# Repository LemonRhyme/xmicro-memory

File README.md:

# XMICRO-MEMORY

[XMICRO](https://github.com/x-microsystems/xmicro-bus) card providing 1MB of RAM and an optional relocatable 8KB EEPROM.

[Datasheet](Documentation/XMICRO-MEMORY.pdf)

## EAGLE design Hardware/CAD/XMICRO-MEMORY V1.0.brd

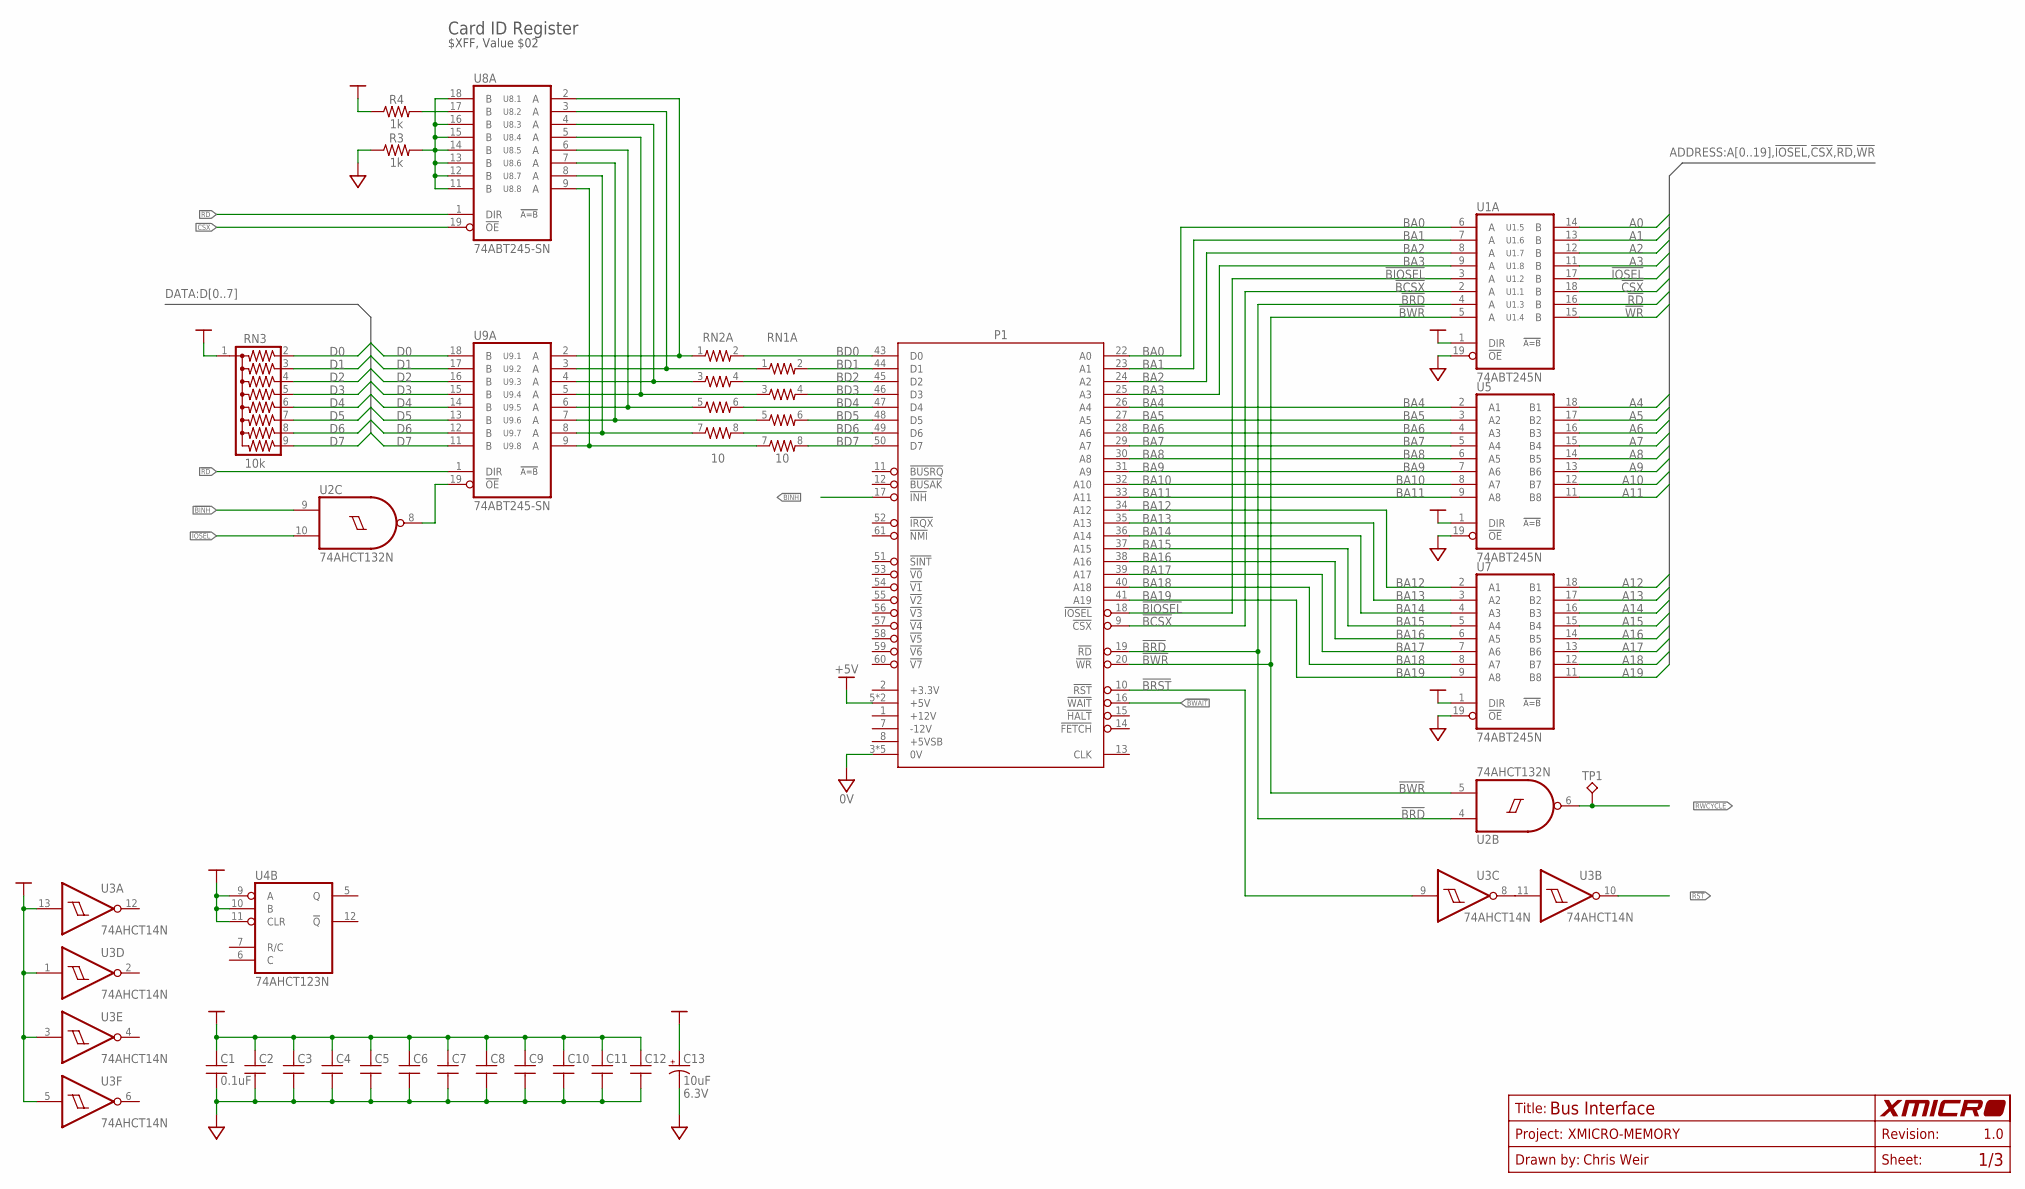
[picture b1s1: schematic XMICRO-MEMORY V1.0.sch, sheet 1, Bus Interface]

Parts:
C1, C2, C3, C4, C5, C6, C7, C8, C9, C10, C11, C12: 0.1uF; C025-024X044
C13: 10uF; E2,5-6; VOLTAGE 6.3V
P1: XMICRO-BUS-EDGE; EDGE62M
R3, R4: 1k; 0207/10
RN1, RN2: 10; SIL8
RN3: 10k; SIL9
TP1: TP-040
U1, U5, U7: 74ABT245N; DIL20
U2: 74AHCT132N; DIL14
U3: 74AHCT14N; DIL14
U4: 74AHCT123N; DIL16
U8, U9: 74ABT245-SN; DIL20

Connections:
0V: C1.2, C2.2, C3.2, C4.2, C5.2, C6.2, C7.2, C8.2, C9.2, C10.2, C11.2, C12.2, C13.-, P1.3 (0V), P1.4 (0V), P1.21 (0V), P1.42 (0V), P1.62 (0V), R3.1, U1.10 (0V), U1.19 (!OE), U2.7 (0V), U3.7 (0V), U4.8 (0V), U5.10 (0V), U5.19 (!OE), U7.10 (0V), U7.19 (!OE), U8.10 (0V), U9.10 (0V); also elsewhere on the board
!BCSX: P1.9 (!CSX), U1.2 (A)
!BINH: P1.17 (!INH), U2.9 (I0); also elsewhere on the board
!BIOSEL: P1.18 (!IOSEL), U1.3 (A)
!BRD: P1.19 (!RD), U1.4 (A), U2.4 (I0)
!BRST: P1.10 (!RST), U3.9 (I)
!BWAIT: P1.16 (!WAIT); also elsewhere on the board
!BWR: P1.20 (!WR), U1.5 (A), U2.5 (I1)
!CSX: U1.18 (B), U8.19 (!OE)
!IOSEL: U1.17 (B), U2.10 (I1); also elsewhere on the board
!RD: U1.16 (B), U8.1 (DIR), U9.1 (DIR); also elsewhere on the board
!RST: U3.10 (O); also elsewhere on the board
!WR: U1.15 (B); also elsewhere on the board
+5V: C1.1, C2.1, C3.1, C4.1, C5.1, C6.1, C7.1, C8.1, C9.1, C10.1, C11.1, C12.1, C13.+, P1.5 (+5V), P1.6 (+5V), R4.1, RN3.1, U1.1 (DIR), U1.20 (+5V), U2.14 (+5V), U3.1 (I), U3.3 (I), U3.5 (I), U3.13 (I), U3.14 (+5V), U4.9 (A), U4.10 (B), U4.11 (CLR), U4.16 (+5V), U5.1 (DIR), U5.20 (+5V), U7.1 (DIR), U7.20 (+5V), U8.20 (+5V), U9.20 (+5V); also elsewhere on the board
A0: U1.14 (B); also elsewhere on the board
A1: U1.13 (B); also elsewhere on the board
A2: U1.12 (B); also elsewhere on the board
A3: U1.11 (B); also elsewhere on the board
A4: U5.18 (B1); also elsewhere on the board
A5: U5.17 (B2); also elsewhere on the board
A6: U5.16 (B3); also elsewhere on the board
A7: U5.15 (B4); also elsewhere on the board
A8: U5.14 (B5); also elsewhere on the board
A9: U5.13 (B6); also elsewhere on the board
A10: U5.12 (B7); also elsewhere on the board
A11: U5.11 (B8); also elsewhere on the board
A12: U7.18 (B1); also elsewhere on the board
A13: U7.17 (B2); also elsewhere on the board
A14: U7.16 (B3); also elsewhere on the board
A15: U7.15 (B4); also elsewhere on the board
A16: U7.14 (B5); also elsewhere on the board
A17: U7.13 (B6); also elsewhere on the board
A18: U7.12 (B7); also elsewhere on the board
A19: U7.11 (B8); also elsewhere on the board
BA0: P1.22 (A0), U1.6 (A)
BA1: P1.23 (A1), U1.7 (A)
BA2: P1.24 (A2), U1.8 (A)
BA3: P1.25 (A3), U1.9 (A)
BA4: P1.26 (A4), U5.2 (A1)
BA5: P1.27 (A5), U5.3 (A2)
BA6: P1.28 (A6), U5.4 (A3)
BA7: P1.29 (A7), U5.5 (A4)
BA8: P1.30 (A8), U5.6 (A5)
BA9: P1.31 (A9), U5.7 (A6)
BA10: P1.32 (A10), U5.8 (A7)
BA11: P1.33 (A11), U5.9 (A8)
BA12: P1.34 (A12), U7.2 (A1)
BA13: P1.35 (A13), U7.3 (A2)
BA14: P1.36 (A14), U7.4 (A3)
BA15: P1.37 (A15), U7.5 (A4)
BA16: P1.38 (A16), U7.6 (A5)
BA17: P1.39 (A17), U7.7 (A6)
BA18: P1.40 (A18), U7.8 (A7)
BA19: P1.41 (A19), U7.9 (A8)
BD0: P1.43 (D0), RN2.2
BD1: P1.44 (D1), RN1.2
BD2: P1.45 (D2), RN2.4 (2)
BD3: P1.46 (D3), RN1.4 (2)
BD4: P1.47 (D4), RN2.6 (2)
BD5: P1.48 (D5), RN1.6 (2)
BD6: P1.49 (D6), RN2.8 (2)
BD7: P1.50 (D7), RN1.8 (2)
D0: RN3.2, U9.18 (B); also elsewhere on the board
D1: RN3.3, U9.17 (B); also elsewhere on the board
D2: RN3.4, U9.16 (B); also elsewhere on the board
D3: RN3.5, U9.15 (B); also elsewhere on the board
D4: RN3.6, U9.14 (B); also elsewhere on the board
D5: RN3.7, U9.13 (B); also elsewhere on the board
D6: RN3.8, U9.12 (B); also elsewhere on the board
D7: RN3.9, U9.11 (B); also elsewhere on the board
unnamed: R3.2, U8.11 (B), U8.12 (B), U8.13 (B), U8.14 (B), U8.15 (B), U8.16 (B), U8.18 (B)
unnamed: R4.2, U8.17 (B)
unnamed: U3.8 (O), U3.11 (I)
unnamed: U2.8 (O), U9.19 (!OE)
unnamed: RN2.1, U8.2 (A), U9.2 (A)
unnamed: RN1.1, U8.3 (A), U9.3 (A)
unnamed: RN2.3 (1), U8.4 (A), U9.4 (A)
unnamed: RN1.3 (1), U8.5 (A), U9.5 (A)
unnamed: RN2.5 (1), U8.6 (A), U9.6 (A)
unnamed: RN1.5 (1), U8.7 (A), U9.7 (A)
unnamed: RN2.7 (1), U8.8 (A), U9.8 (A)
unnamed: RN1.7 (1), U8.9 (A), U9.9 (A)
RWCYCLE: TP1.1, U2.6 (O); also elsewhere on the board

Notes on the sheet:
Card ID Register
$XFF, Value $02

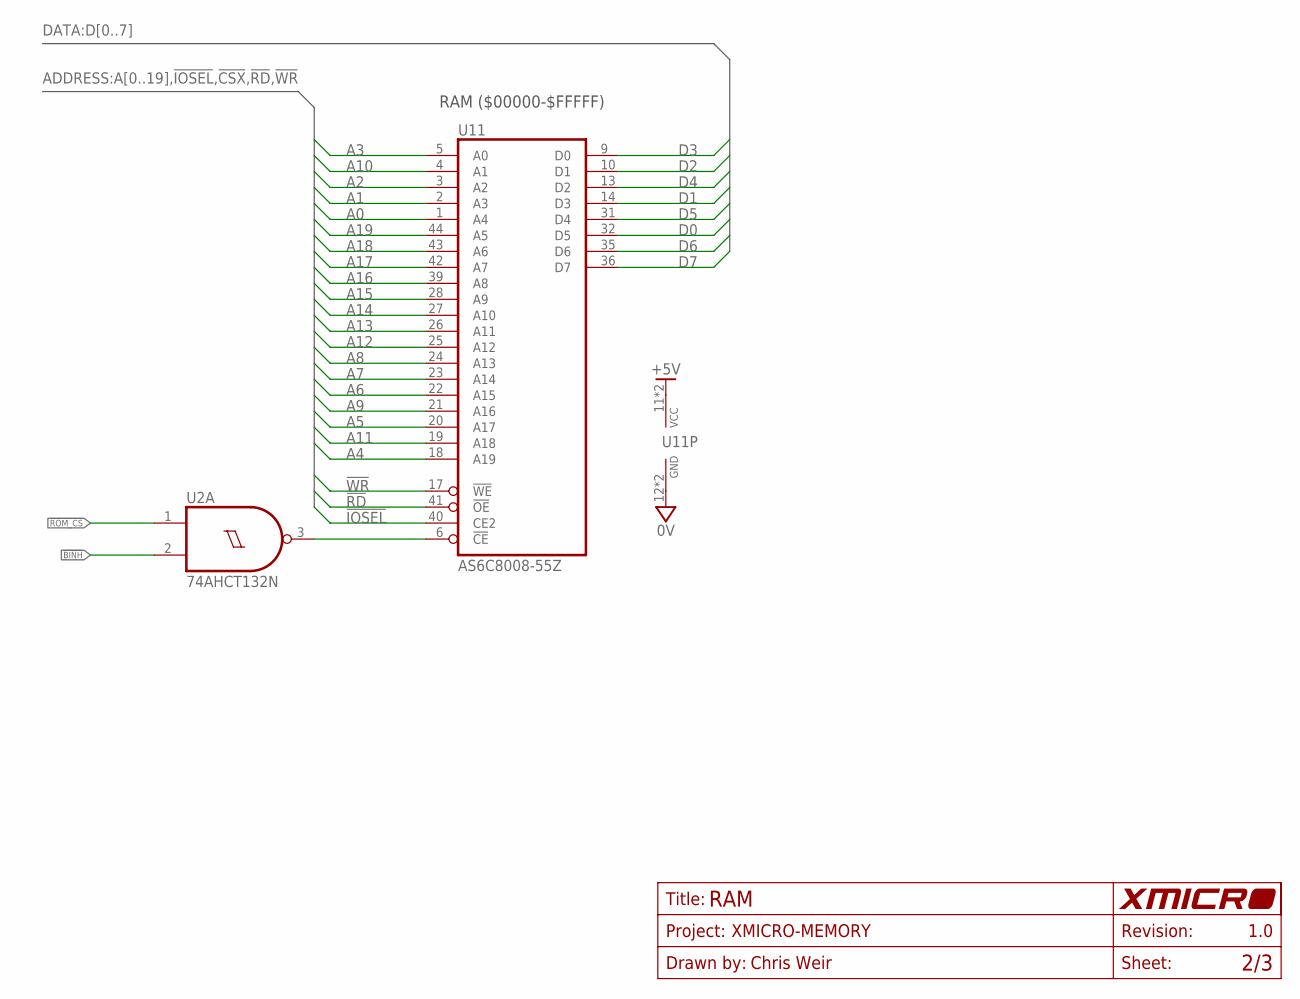
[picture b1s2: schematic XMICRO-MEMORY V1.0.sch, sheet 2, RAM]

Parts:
U2: 74AHCT132N; DIL14
U11: AS6C8008-55Z; TSOP44-II

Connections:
0V: U2.7 (0V), U11.12 (0V), U11.34 (0V); also elsewhere on the board
!BINH: U2.2 (I1); also elsewhere on the board
!IOSEL: U11.40 (CE2); also elsewhere on the board
!RD: U11.41 (!OE); also elsewhere on the board
!ROM_CS: U2.1 (I0); also elsewhere on the board
!WR: U11.17 (!WE); also elsewhere on the board
+5V: U2.14 (+5V), U11.11 (+5V), U11.33 (+5V); also elsewhere on the board
A0: U11.1 (A4); also elsewhere on the board
A1: U11.2 (A3); also elsewhere on the board
A2: U11.3 (A2); also elsewhere on the board
A3: U11.5 (A0); also elsewhere on the board
A4: U11.18 (A19); also elsewhere on the board
A5: U11.20 (A17); also elsewhere on the board
A6: U11.22 (A15); also elsewhere on the board
A7: U11.23 (A14); also elsewhere on the board
A8: U11.24 (A13); also elsewhere on the board
A9: U11.21 (A16); also elsewhere on the board
A10: U11.4 (A1); also elsewhere on the board
A11: U11.19 (A18); also elsewhere on the board
A12: U11.25 (A12); also elsewhere on the board
A13: U11.26 (A11); also elsewhere on the board
A14: U11.27 (A10); also elsewhere on the board
A15: U11.28 (A9); also elsewhere on the board
A16: U11.39 (A8); also elsewhere on the board
A17: U11.42 (A7); also elsewhere on the board
A18: U11.43 (A6); also elsewhere on the board
A19: U11.44 (A5); also elsewhere on the board
D0: U11.32 (D5); also elsewhere on the board
D1: U11.14 (D3); also elsewhere on the board
D2: U11.10 (D1); also elsewhere on the board
D3: U11.9 (D0); also elsewhere on the board
D4: U11.13 (D2); also elsewhere on the board
D5: U11.31 (D4); also elsewhere on the board
D6: U11.35 (D6); also elsewhere on the board
D7: U11.36 (D7); also elsewhere on the board
unnamed: U2.3 (O), U11.6 (!CE)

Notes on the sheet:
RAM ($00000-$FFFFF)

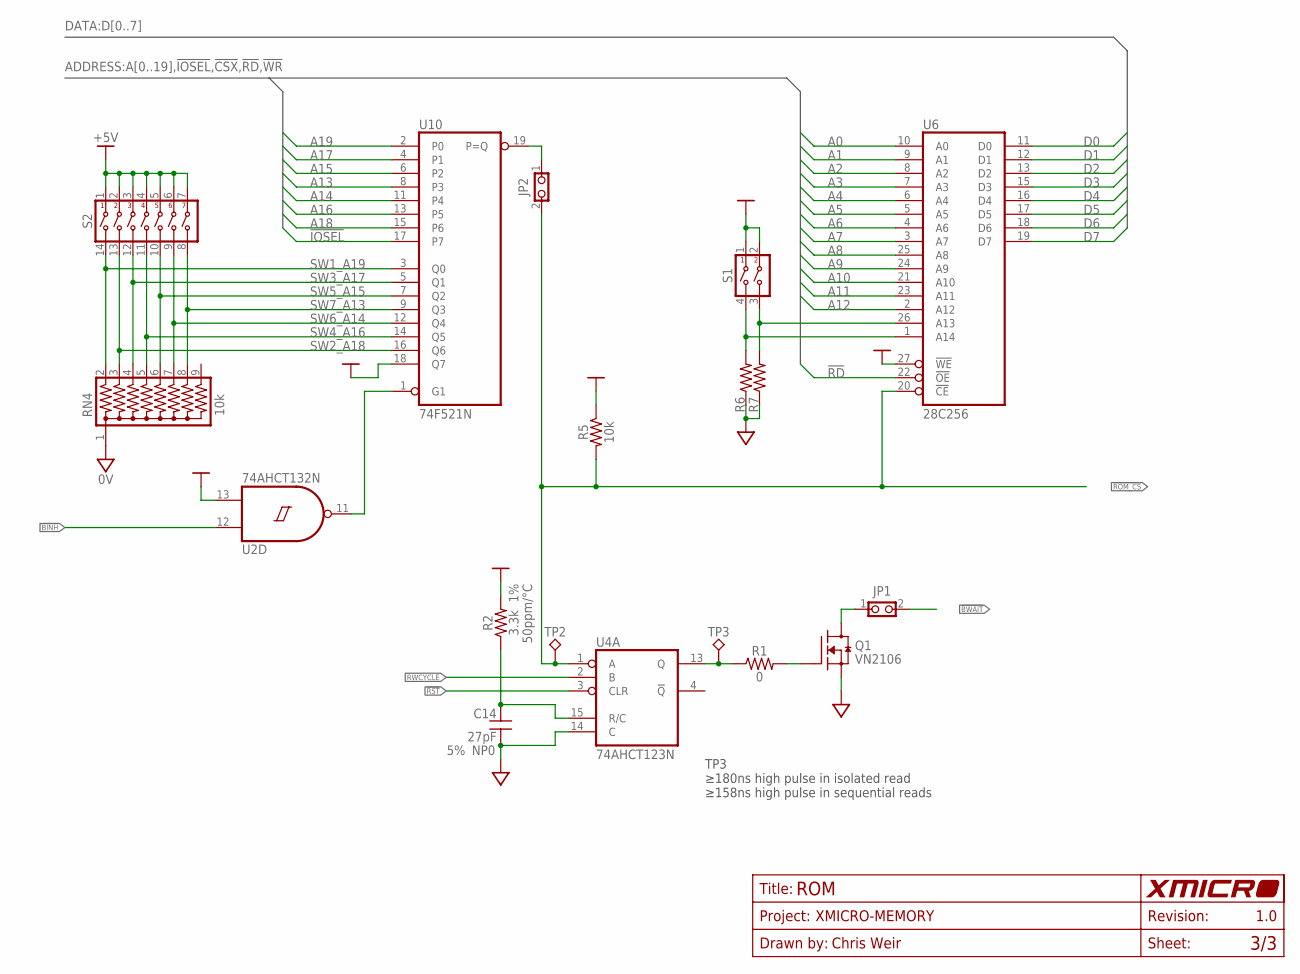
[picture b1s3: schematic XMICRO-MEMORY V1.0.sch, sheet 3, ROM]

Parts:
C14: 27pF; C025-024X044; TOLERANCE 5%
JP1, JP2: 1X2-THRU; 1X2
Q1: VN2106; TO92
R1: 0; 0207/10
R2: 3.3k; 0207/10; TOLERANCE 1%
R5, R6, R7: 10k; 0207/10
RN4: 10k; SIL9
S1: SW-DIP02; SW-DIP2
S2: SW-DIP07; SW-DIP7
TP2, TP3: TP-040
U2: 74AHCT132N; DIL14
U4: 74AHCT123N; DIL16
U6: 28C256; 228-1277-00
U10: 74F521N; DIL20

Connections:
0V: C14.2, Q1.1 (S), R6.1, R7.1, RN4.1, U2.7 (0V), U4.8 (0V), U4.14 (C), U6.14 (0V), U10.10 (0V); also elsewhere on the board
!BINH: U2.12 (I0); also elsewhere on the board
!BWAIT: JP1.2; also elsewhere on the board
!IOSEL: U10.17 (P7); also elsewhere on the board
!RD: U6.22 (!OE); also elsewhere on the board
!ROM_CS: JP2.2, R5.2, TP2.1, U4.1 (A), U6.20 (!CE); also elsewhere on the board
!RST: U4.3 (CLR); also elsewhere on the board
+5V: R2.2, R5.1, S1.1, S1.2, S2.1, S2.2, S2.3, S2.4, S2.5, S2.6, S2.7, U2.13 (I1), U2.14 (+5V), U4.16 (+5V), U6.27 (!WE), U6.28 (+5V), U10.18 (Q7), U10.20 (+5V); also elsewhere on the board
A0: U6.10 (A0); also elsewhere on the board
A1: U6.9 (A1); also elsewhere on the board
A2: U6.8 (A2); also elsewhere on the board
A3: U6.7 (A3); also elsewhere on the board
A4: U6.6 (A4); also elsewhere on the board
A5: U6.5 (A5); also elsewhere on the board
A6: U6.4 (A6); also elsewhere on the board
A7: U6.3 (A7); also elsewhere on the board
A8: U6.25 (A8); also elsewhere on the board
A9: U6.24 (A9); also elsewhere on the board
A10: U6.21 (A10); also elsewhere on the board
A11: U6.23 (A11); also elsewhere on the board
A12: U6.2 (A12); also elsewhere on the board
A13: U10.8 (P3); also elsewhere on the board
A14: U10.11 (P4); also elsewhere on the board
A15: U10.6 (P2); also elsewhere on the board
A16: U10.13 (P5); also elsewhere on the board
A17: U10.4 (P1); also elsewhere on the board
A18: U10.15 (P6); also elsewhere on the board
A19: U10.2 (P0); also elsewhere on the board
D0: U6.11 (D0); also elsewhere on the board
D1: U6.12 (D1); also elsewhere on the board
D2: U6.13 (D2); also elsewhere on the board
D3: U6.15 (D3); also elsewhere on the board
D4: U6.16 (D4); also elsewhere on the board
D5: U6.17 (D5); also elsewhere on the board
D6: U6.18 (D6); also elsewhere on the board
D7: U6.19 (D7); also elsewhere on the board
unnamed: JP2.1, U10.19 (P=Q)
unnamed: Q1.2 (G), R1.2
unnamed: JP1.1, Q1.3 (D)
unnamed: R7.2, S1.3, U6.26 (A13)
unnamed: R6.2, S1.4, U6.1 (A14)
unnamed: U2.11 (O), U10.1 (G1)
unnamed: C14.1, R2.1, U4.15 (R/C)
RWCYCLE: U4.2 (B); also elsewhere on the board
SW1_A19: RN4.2, S2.14, U10.3 (Q0)
SW2_A18: RN4.3, S2.13, U10.16 (Q6)
SW3_A17: RN4.4, S2.12, U10.5 (Q1)
SW4_A16: RN4.5, S2.11, U10.14 (Q5)
SW5_A15: RN4.6, S2.10, U10.7 (Q2)
SW6_A14: RN4.7, S2.9, U10.12 (Q4)
SW7_A13: RN4.8, S2.8, U10.9 (Q3)
WAIT_ROM: R1.1, TP3.1, U4.13 (Q)

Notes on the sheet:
TP3 ≥180ns high pulse in isolated read ≥158ns high pulse in sequential reads

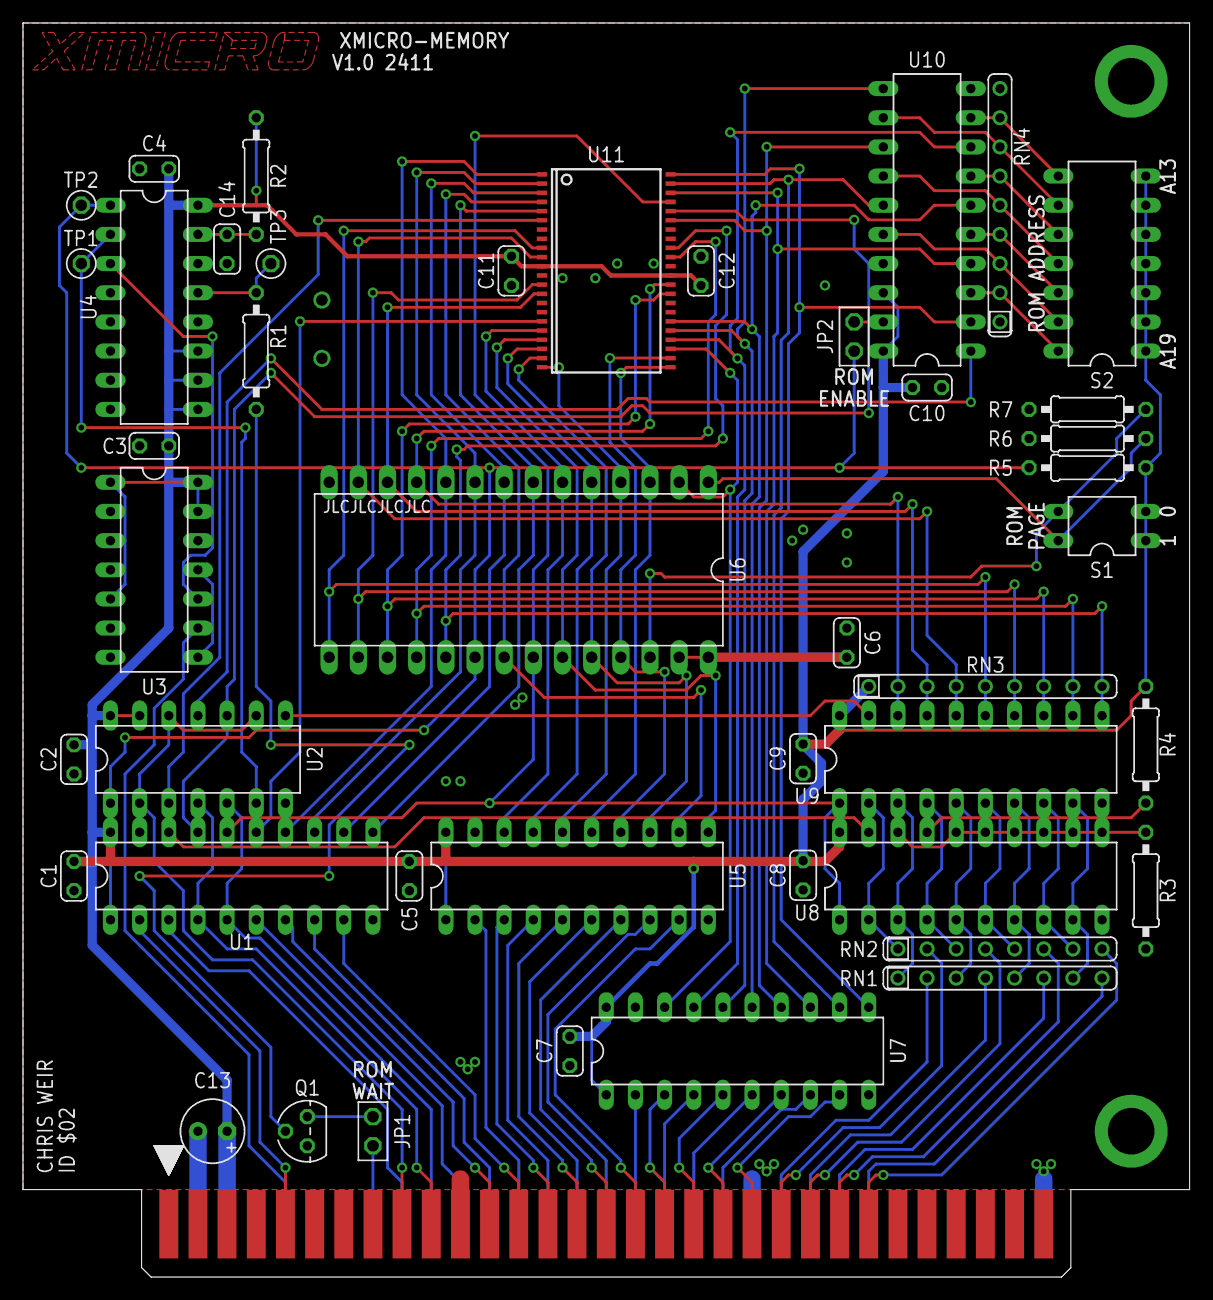
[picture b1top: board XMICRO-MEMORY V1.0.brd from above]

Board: 2 copper layers, 101.6 x 109.2 mm, 45 parts (0 on the bottom side), 100 nets.
